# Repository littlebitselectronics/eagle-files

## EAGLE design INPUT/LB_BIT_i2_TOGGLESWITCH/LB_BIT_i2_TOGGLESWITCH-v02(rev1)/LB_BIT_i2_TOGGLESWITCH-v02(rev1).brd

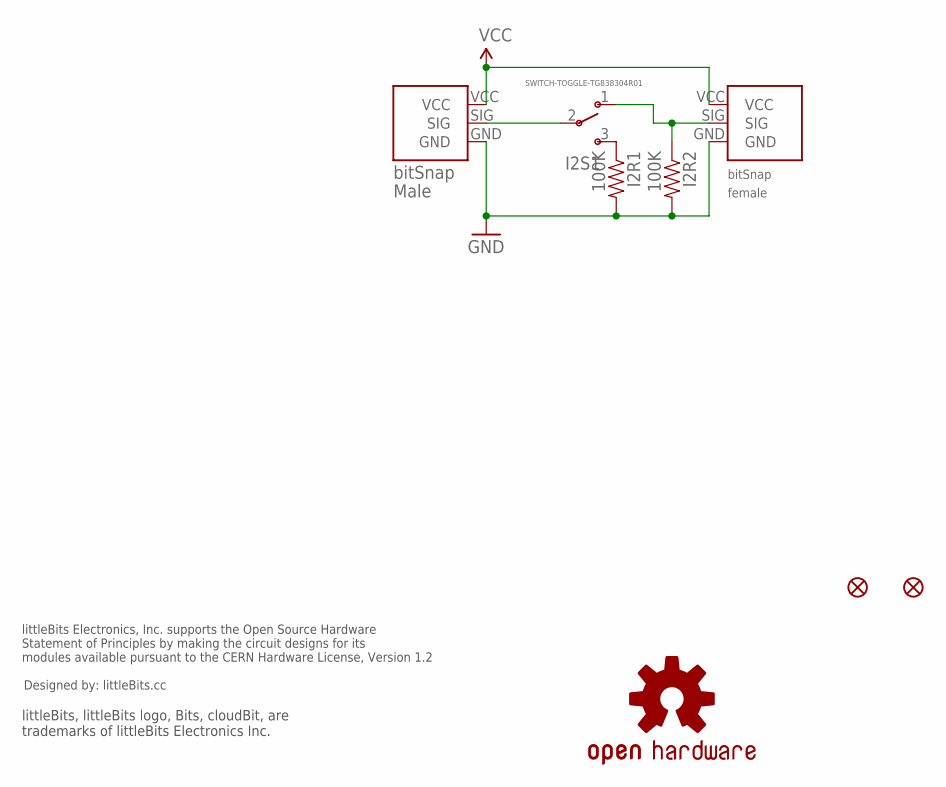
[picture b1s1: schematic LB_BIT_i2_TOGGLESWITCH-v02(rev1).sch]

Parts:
I2BSF: BITSNAP_FEMALE
I2BSM: BITSNAP_MALE
I2R1, I2R2: 100K; 0603-RES
I2S1: SWITCH-TOGGLE-TG838304R01
JP1, JP2: FIDUCIAL1X2; FIDUCIAL-1X2
U$4: OSHWCREDIT
U$7: OSHW-LOGOL; OSHW-LOGO-L

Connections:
GND: I2BSF.GND, I2BSM.GND, I2R1.2, I2R2.2
unnamed: I2R1.1, I2S1.3 (S)
unnamed: I2BSM.SIG, I2S1.2
unnamed: I2BSF.SIG, I2R2.1, I2S1.1 (O)
VCC: I2BSF.VCC, I2BSM.VCC

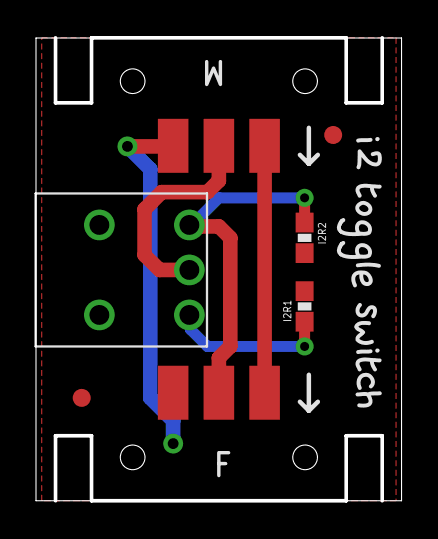
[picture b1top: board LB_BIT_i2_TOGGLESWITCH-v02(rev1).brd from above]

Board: 2 copper layers, 20.3 x 25.7 mm, 24 parts (0 on the bottom side), 5 nets.

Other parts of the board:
U$1, U$29: I
U$2: 2
U$3, U$30: T
U$6: OSHW_FILLX150_NOTEXT
U$22: O
U$23, U$24: G
U$25: L
U$26: E
U$27: S
U$28: W
U$31: C
U$32: H

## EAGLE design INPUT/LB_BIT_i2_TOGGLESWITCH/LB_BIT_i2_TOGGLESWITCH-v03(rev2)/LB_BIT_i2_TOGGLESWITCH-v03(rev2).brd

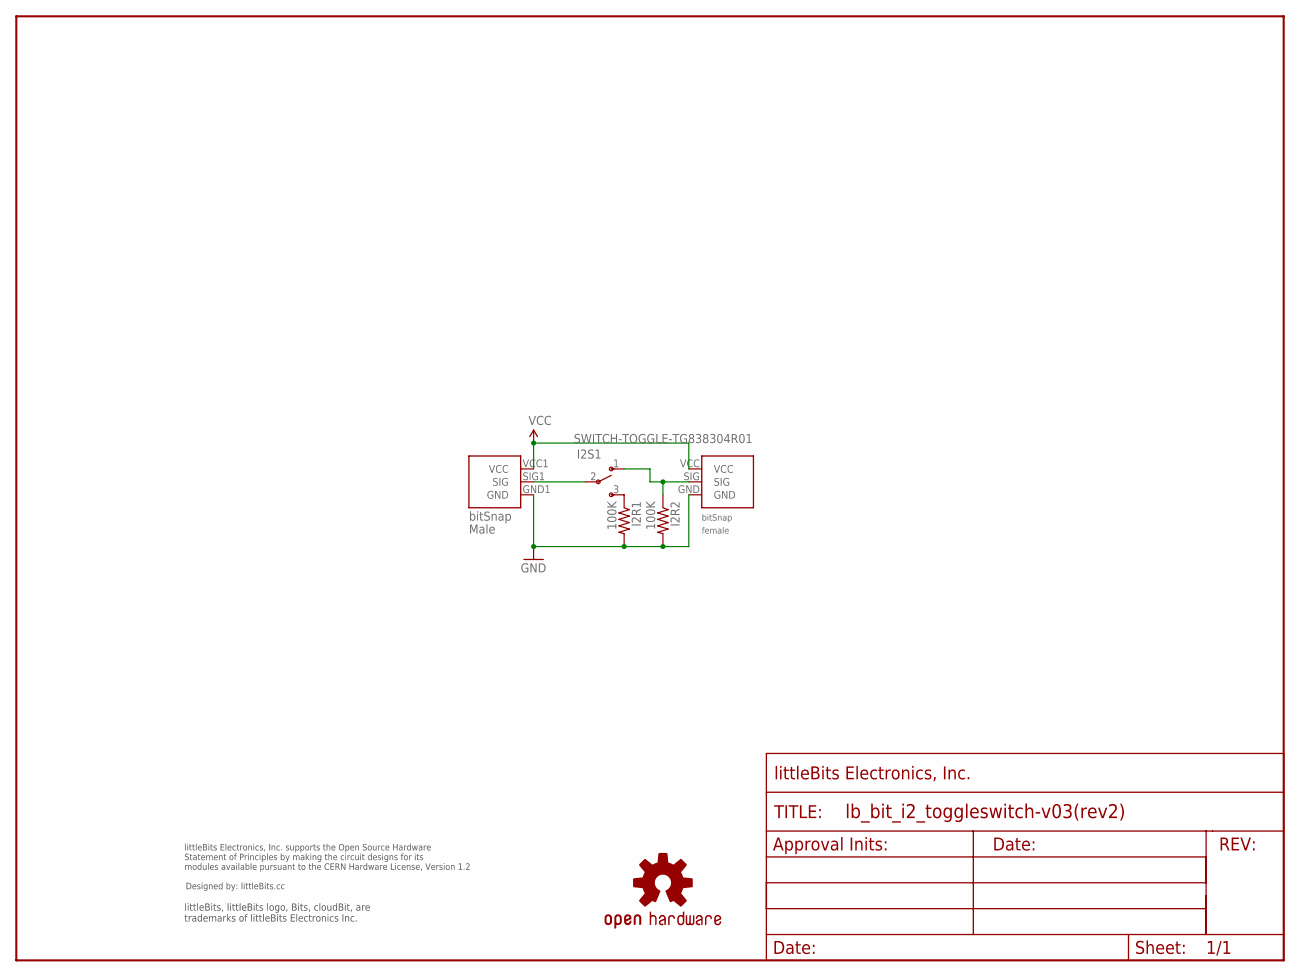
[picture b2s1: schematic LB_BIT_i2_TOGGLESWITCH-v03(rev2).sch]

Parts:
FRAME1: FRAME-LETTER-OHWOHW; FABDWG01-OHW
I2BSF1: BITSNAP_V03_FEMALE
I2BSM1: BITSNAP_V03_MALE
I2R1, I2R2: 100K; 0603-RES
I2S1: SWITCH-TOGGLE-TG838304R01
U$2: OSHWCREDIT
U$7: OSHW-LOGOL; OSHW-LOGO-L

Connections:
GND: I2BSF1.GND, I2BSM1.GND1 (GND), I2R1.2, I2R2.2
unnamed: I2R1.1, I2S1.3 (S)
unnamed: I2BSM1.SIG1 (SIG), I2S1.2
unnamed: I2BSF1.SIG, I2R2.1, I2S1.1 (O)
VCC: I2BSF1.VCC, I2BSM1.VCC1 (VCC)

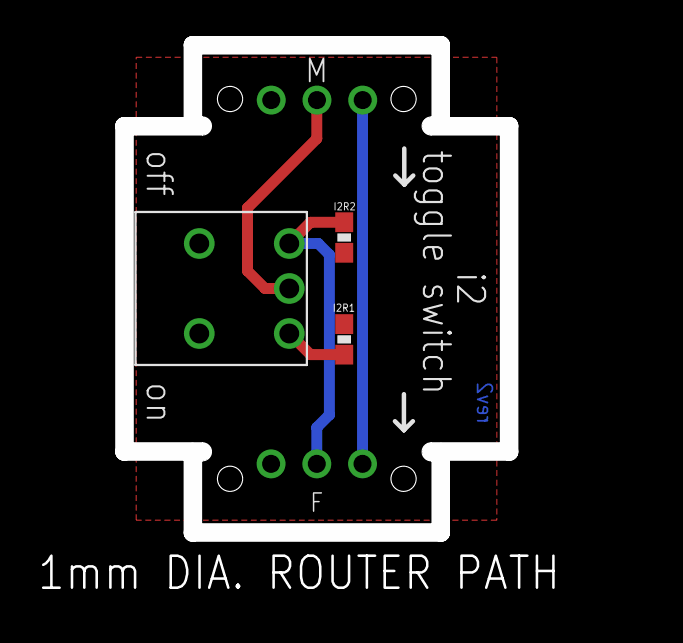
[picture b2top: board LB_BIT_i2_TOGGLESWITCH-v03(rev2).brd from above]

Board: 2 copper layers, 21.4 x 27.1 mm, 9 parts (0 on the bottom side), 5 nets.

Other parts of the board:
U$6: OSHW_FILLX150_NOTEXT

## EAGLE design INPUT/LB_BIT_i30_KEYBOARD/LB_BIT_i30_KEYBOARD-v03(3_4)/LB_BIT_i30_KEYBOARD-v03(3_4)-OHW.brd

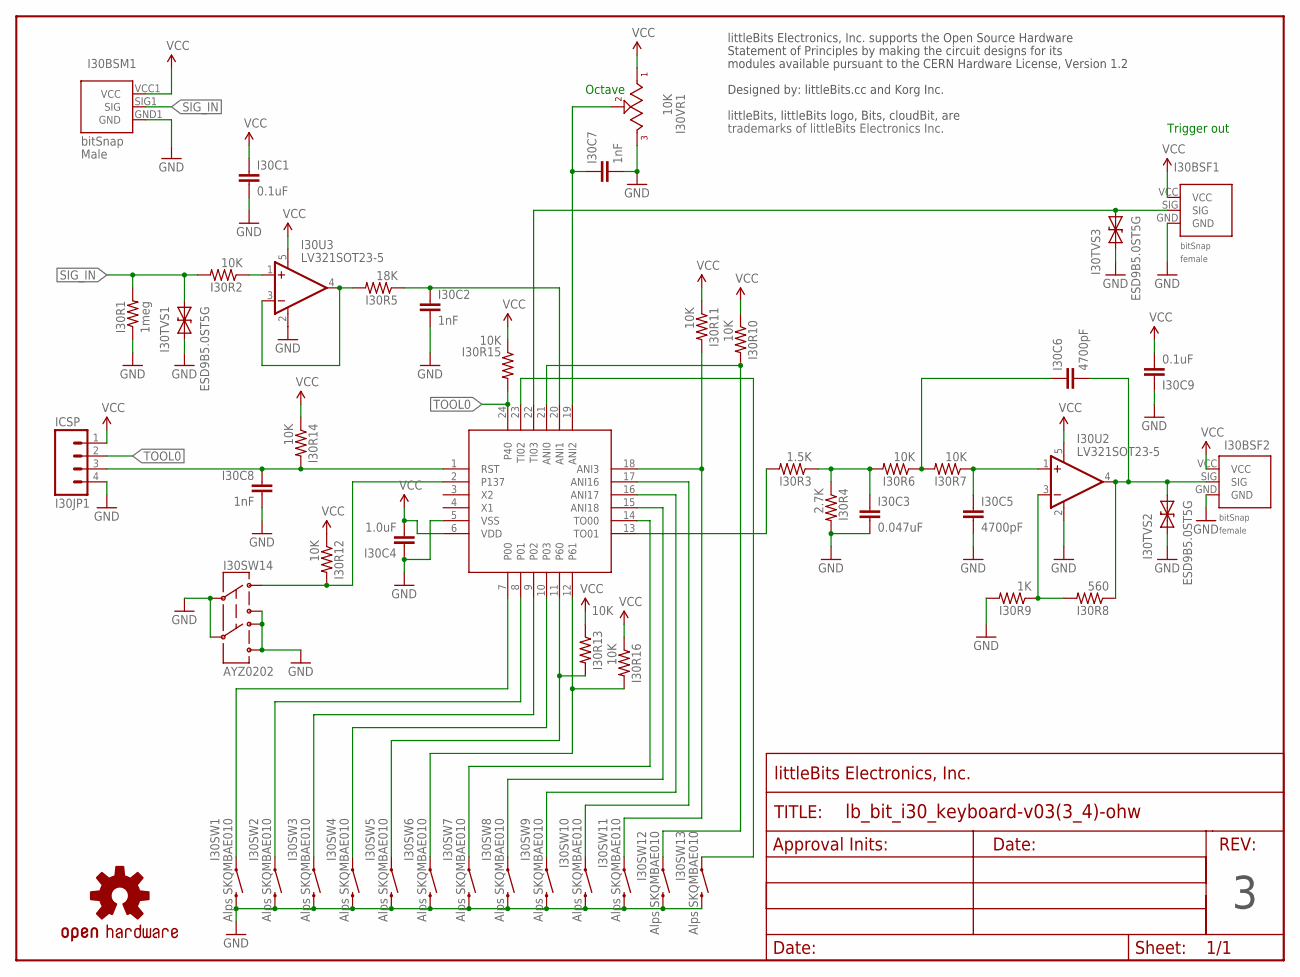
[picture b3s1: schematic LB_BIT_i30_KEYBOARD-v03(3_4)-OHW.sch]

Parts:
FRAME1: FRAME-LETTER-OHWOHW; FABDWG01-OHW
I30BSF1, I30BSF2: BITSNAP_V03_FEMALE
I30BSM1: BITSNAP_V03_MALE
I30C1, I30C9: 0.1uF; CAP-0603
I30C2, I30C7, I30C8: 1nF; CAP-0603
I30C3: 0.047uF; CAP-0603
I30C4: 1.0uF; CAP-0603
I30C5, I30C6: 4700pF; CAP-0603
I30JP1: ICSP; SIP4-SM-0.1IN-NOS.S.
I30R1: 1meg; RES-0603
I30R2, I30R6, I30R7, I30R10, I30R11, I30R12, I30R13, I30R14, I30R15, I30R16: 10K; RES-0603
I30R3: 1.5K; RES-0603
I30R4: 2.7K; RES-0603
I30R5: 18K; RES-0603
I30R8: 560; RES-0603
I30R9: 1K; RES-0603
I30SW1, I30SW2, I30SW3, I30SW4, I30SW5, I30SW6, I30SW7, I30SW8, I30SW9, I30SW10, I30SW11, I30SW12, I30SW13: Alps SKQMBAE010; TACTILE-SWITCH-EVQ-PE104K
I30SW14: AYZ0202
I30TVS1, I30TVS2, I30TVS3: ESD9B5.0ST5G; SOD-923
I30U1: R5F10278QFN-24; QFN-24(4MM)
I30U2, I30U3: LV321SOT23-5; SOT23-5
I30VR1: 10K; THUMBPOT-BOURNS_3352
U$1: OSHW-LOGOL; OSHW-LOGO-L
U$2: OSHWCREDIT-KORG

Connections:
GND: I30BSF1.GND, I30BSF2.GND, I30BSM1.GND1 (GND), I30C1.2, I30C2.2, I30C3.2, I30C4.1, I30C5.2, I30C7.2, I30C8.2, I30C9.1, I30JP1.4, I30R1.1, I30R4.2, I30R9.2, I30SW1.P$2 (2), I30SW2.P$2 (2), I30SW3.P$2 (2), I30SW4.P$2 (2), I30SW5.P$2 (2), I30SW6.P$2 (2), I30SW7.P$2 (2), I30SW8.P$2 (2), I30SW9.P$2 (2), I30SW10.P$2 (2), I30SW11.P$2 (2), I30SW12.P$2 (2), I30SW13.P$2 (2), I30SW14.2, I30SW14.3, I30SW14.4, I30SW14.5, I30SW14.6, I30TVS1.1 (A), I30TVS2.1 (A), I30TVS3.1 (A), I30U1.5 (VSS), I30U2.2 (V-), I30U3.2 (V-), I30VR1.1 (3)
unnamed: I30C2.1, I30R5.1, I30U1.20 (ANI1)
unnamed: I30R5.2, I30U3.3 (-IN), I30U3.4 (OUT)
unnamed: I30C3.1, I30R3.1, I30R4.1, I30R6.2
unnamed: I30R2.1, I30U3.1 (+IN)
unnamed: I30R3.2, I30U1.13 (TO01)
unnamed: I30R8.2, I30R9.1, I30U2.3 (-IN)
unnamed: I30C6.1, I30R6.1, I30R7.2
unnamed: I30BSF1.SIG, I30TVS3.2 (C), I30U1.22 (TI03)
unnamed: I30SW13.P$1 (1), I30U1.23 (TI02)
unnamed: I30C5.1, I30R7.1, I30U2.1 (+IN)
unnamed: I30R12.2, I30SW14.1, I30U1.2 (P137)
unnamed: I30R10.2, I30SW12.P$1 (1), I30U1.21 (ANI0)
unnamed: I30R11.2, I30SW11.P$1 (1), I30U1.18 (ANI3)
unnamed: I30SW10.P$1 (1), I30U1.17 (ANI16)
unnamed: I30SW9.P$1 (1), I30U1.16 (ANI17)
unnamed: I30SW8.P$1 (1), I30U1.15 (ANI18)
unnamed: I30SW7.P$1 (1), I30U1.14 (TO00)
unnamed: I30R16.2, I30SW6.P$1 (1), I30U1.12 (P61)
unnamed: I30R13.2, I30SW5.P$1 (1), I30U1.11 (P60)
unnamed: I30SW4.P$1 (1), I30U1.10 (P03)
unnamed: I30SW3.P$1 (1), I30U1.9 (P02)
unnamed: I30SW2.P$1 (1), I30U1.8 (P01)
unnamed: I30SW1.P$1 (1), I30U1.7 (P00)
unnamed: I30C7.1, I30U1.19 (ANI2), I30VR1.2
unnamed: I30C8.1, I30JP1.3, I30R14.2, I30U1.1 (RST)
SIG_IN: I30BSM1.SIG1 (SIG), I30R1.2, I30R2.2, I30TVS1.2 (C)
SIG_OUT: I30BSF2.SIG, I30C6.2, I30R8.1, I30TVS2.2 (C), I30U2.4 (OUT)
TOOL0: I30JP1.2, I30R15.2, I30U1.24 (P40)
VCC: I30BSF1.VCC, I30BSF2.VCC, I30BSM1.VCC1 (VCC), I30C1.1, I30C4.2, I30C9.2, I30JP1.1, I30R10.1, I30R11.1, I30R12.1, I30R13.1, I30R14.1, I30R15.1, I30R16.1, I30U1.6 (VDD), I30U2.5 (V+), I30U3.5 (V+), I30VR1.3 (1)

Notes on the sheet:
Octave
Trigger out

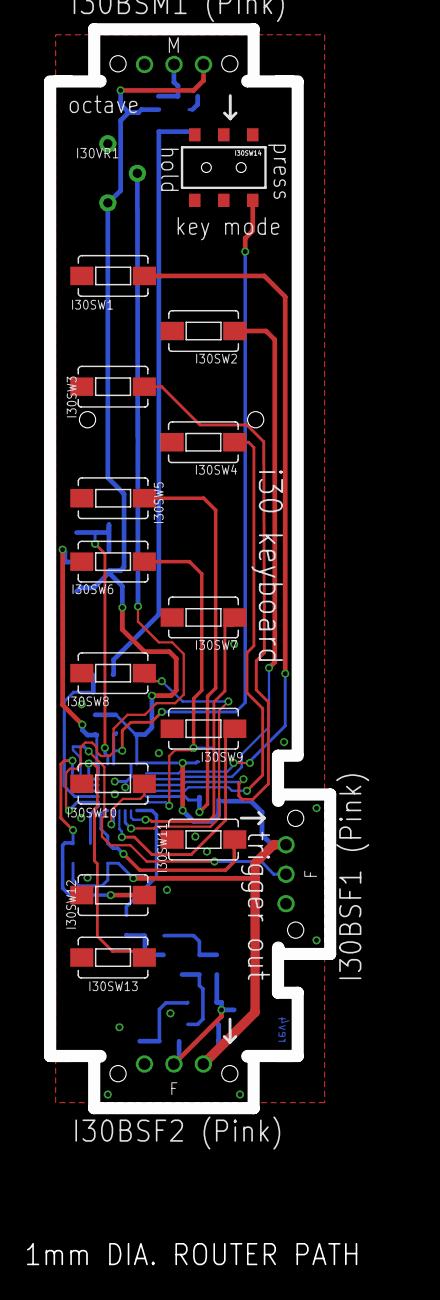
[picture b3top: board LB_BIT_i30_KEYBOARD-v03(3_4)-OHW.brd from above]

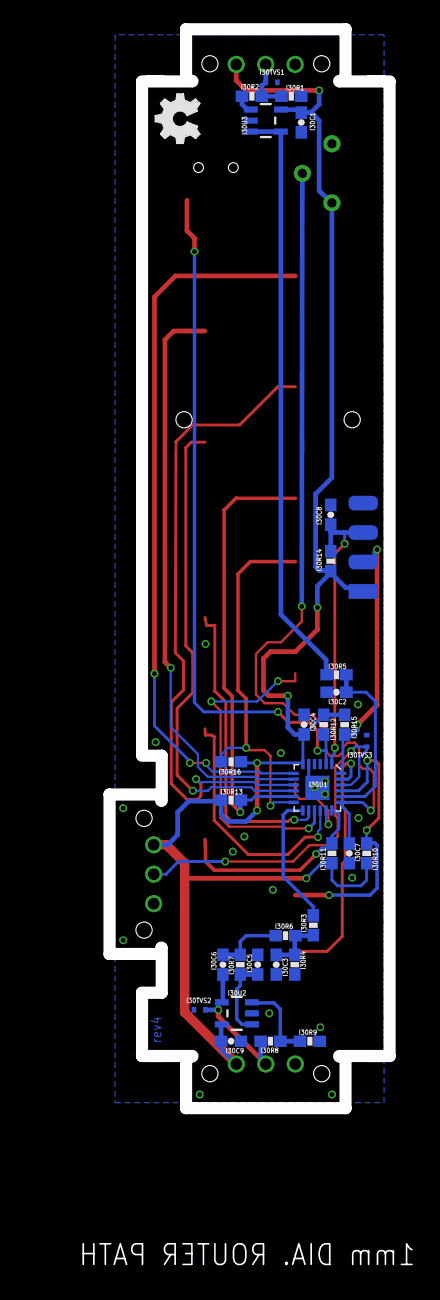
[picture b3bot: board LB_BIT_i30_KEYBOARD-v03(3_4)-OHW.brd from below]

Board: 2 copper layers, 23.2 x 92.1 mm, 55 parts (32 on the bottom side), 30 nets.

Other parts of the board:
U$4: LB_PWR_LEGS
U$17: OSHW_FILLX150_NOTEXT

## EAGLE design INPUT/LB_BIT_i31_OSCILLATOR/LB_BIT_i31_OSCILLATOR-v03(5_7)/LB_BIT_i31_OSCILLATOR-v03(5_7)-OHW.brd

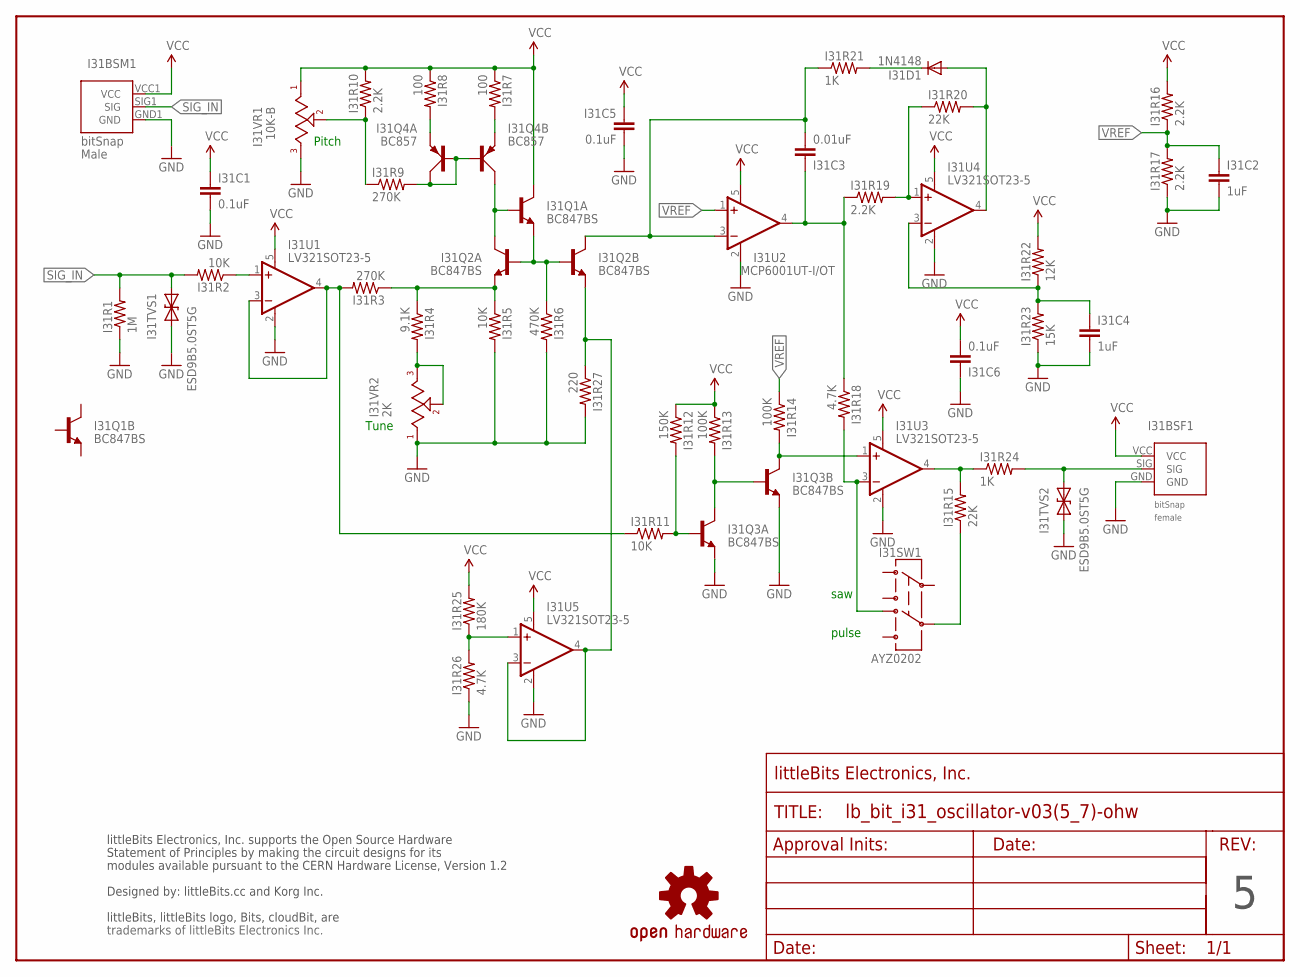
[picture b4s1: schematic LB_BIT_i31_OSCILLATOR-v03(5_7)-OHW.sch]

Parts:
I31BSF1: BITSNAP_V03_FEMALE
I31BSM1: BITSNAP_V03_MALE
I31C1, I31C5, I31C6: 0.1uF; CAP-0603
I31C2, I31C4: 1uF; CAP-0603
I31C3: 0.01uF; CAP-0603
I31D1: 1N4148; SOD-323
I31Q1, I31Q2, I31Q3: BC847BS; SOT-363_PHILLIPS
I31Q4: BC857; SOT-363_PHILLIPS
I31R1: 1M; RES-0603
I31R2, I31R5, I31R11: 10K; RES-0603
I31R3, I31R9: 270K; RES-0603
I31R4: 9.1K; RES-0603
I31R6: 470K; RES-0603
I31R7, I31R8: 100; RES-0603
I31R10, I31R16, I31R17, I31R19: 2.2K; RES-0603
I31R12: 150K; RES-0603
I31R13, I31R14: 100K; RES-0603
I31R15, I31R20: 22K; RES-0603
I31R18, I31R26: 4.7K; RES-0603
I31R21, I31R24: 1K; RES-0603
I31R22: 12K; RES-0603
I31R23: 15K; RES-0603
I31R25: 180K; RES-0603
I31R27: 220; RES-0603
I31SW1: AYZ0202
I31TVS1, I31TVS2: ESD9B5.0ST5G; SOD-923
I31U1, I31U3, I31U4, I31U5: LV321SOT23-5; SOT23-5
I31U2: MCP6001UT; SOT23-5
I31VR1: 10K-B; ALPS_POT
I31VR2: 2K; THUMBPOT-BOURNS_3352
U$2: FRAME-LETTER-OHWOHW; FABDWG01-OHW
U$3: OSHW-LOGOL; OSHW-LOGO-L
U$4: OSHWCREDIT-KORG

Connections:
GND: I31BSF1.GND, I31BSM1.GND1 (GND), I31C1.2, I31C2.2, I31C4.2, I31C5.2, I31C6.1, I31Q3.1 (E), I31Q3.4 (E), I31R1.1, I31R5.2, I31R6.2, I31R17.1, I31R23.1, I31R26.1, I31R27.2, I31TVS1.1 (A), I31TVS2.1 (A), I31U1.2 (V-), I31U2.2 (V-), I31U3.2 (V-), I31U4.2 (V-), I31U5.2 (V-), I31VR1.3, I31VR2.3 (1)
unnamed: I31R4.2, I31VR2.1 (3), I31VR2.2
unnamed: I31R3.2, I31R11.1, I31U1.3 (-IN), I31U1.4 (OUT)
unnamed: I31Q1.2 (B), I31Q2.6 (C), I31Q4.3 (C)
unnamed: I31R2.1, I31U1.1 (+IN)
unnamed: I31Q1.1 (E), I31Q2.2 (B), I31Q2.5 (B), I31R6.1
unnamed: I31Q4.1 (E), I31R8.2
unnamed: I31Q4.4 (E), I31R7.2
unnamed: I31Q2.1 (E), I31R3.1, I31R4.1, I31R5.1
unnamed: I31R18.2, I31SW1.4, I31U3.3 (-IN)
unnamed: I31Q3.2 (B), I31R11.2, I31R12.2
unnamed: I31R19.2, I31R20.1, I31U4.1 (+IN)
unnamed: I31Q4.2 (B), I31Q4.5 (B), I31Q4.6 (C), I31R9.2
unnamed: I31R9.1, I31R10.1, I31VR1.2
unnamed: I31Q3.5 (B), I31Q3.6 (C), I31R13.2
unnamed: I31C3.1, I31R18.1, I31R19.1, I31U2.4 (OUT)
unnamed: I31Q3.3 (C), I31R14.2, I31U3.1 (+IN)
unnamed: I31R15.1, I31SW1.5
unnamed: I31C3.2, I31Q2.3 (C), I31R21.1, I31U2.3 (-IN)
unnamed: I31D1.2 (A), I31R20.2, I31U4.4 (OUT)
unnamed: I31D1.1 (C), I31R21.2
unnamed: I31R15.2, I31R24.1, I31U3.4 (OUT)
unnamed: I31C4.1, I31R22.1, I31R23.2, I31U4.3 (-IN)
unnamed: I31Q2.4 (E), I31R27.1, I31U5.3 (-IN), I31U5.4 (OUT)
unnamed: I31R25.1, I31R26.2, I31U5.1 (+IN)
SIG_IN: I31BSM1.SIG1 (SIG), I31R1.2, I31R2.2, I31TVS1.2 (C)
SIG_OUT: I31BSF1.SIG, I31R24.2, I31TVS2.2 (C)
VCC: I31BSF1.VCC, I31BSM1.VCC1 (VCC), I31C1.1, I31C5.1, I31C6.2, I31Q1.6 (C), I31R7.1, I31R8.1, I31R10.2, I31R12.1, I31R13.1, I31R16.2, I31R22.2, I31R25.2, I31U1.5 (V+), I31U2.5 (V+), I31U3.5 (V+), I31U4.5 (V+), I31U5.5 (V+), I31VR1.1
VREF: I31C2.1, I31R14.1, I31R16.1, I31R17.2, I31U2.1 (+IN)

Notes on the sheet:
pulse
saw
Pitch
Tune
MCP6001UT-I/OT

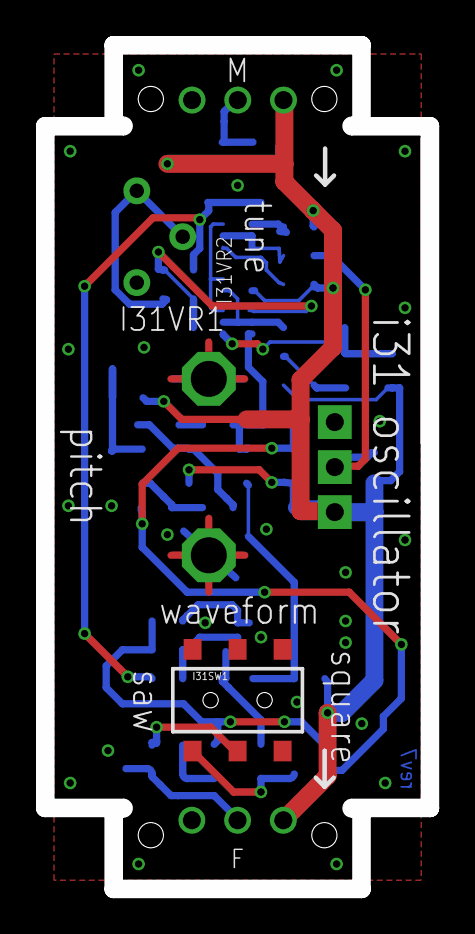
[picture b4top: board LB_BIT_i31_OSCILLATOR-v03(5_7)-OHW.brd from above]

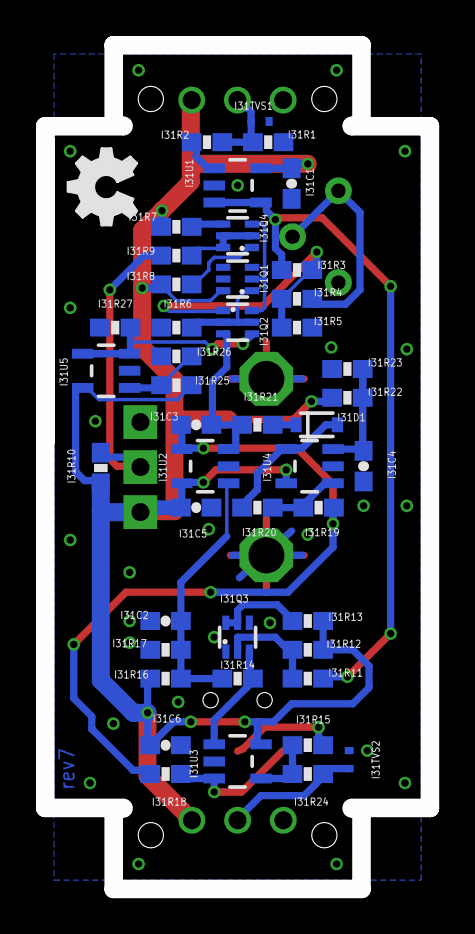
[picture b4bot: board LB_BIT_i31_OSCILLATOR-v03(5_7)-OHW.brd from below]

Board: 2 copper layers, 21.4 x 46.9 mm, 54 parts (45 on the bottom side), 29 nets.

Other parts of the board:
U$8: OSHW_FILLX150_NOTEXT

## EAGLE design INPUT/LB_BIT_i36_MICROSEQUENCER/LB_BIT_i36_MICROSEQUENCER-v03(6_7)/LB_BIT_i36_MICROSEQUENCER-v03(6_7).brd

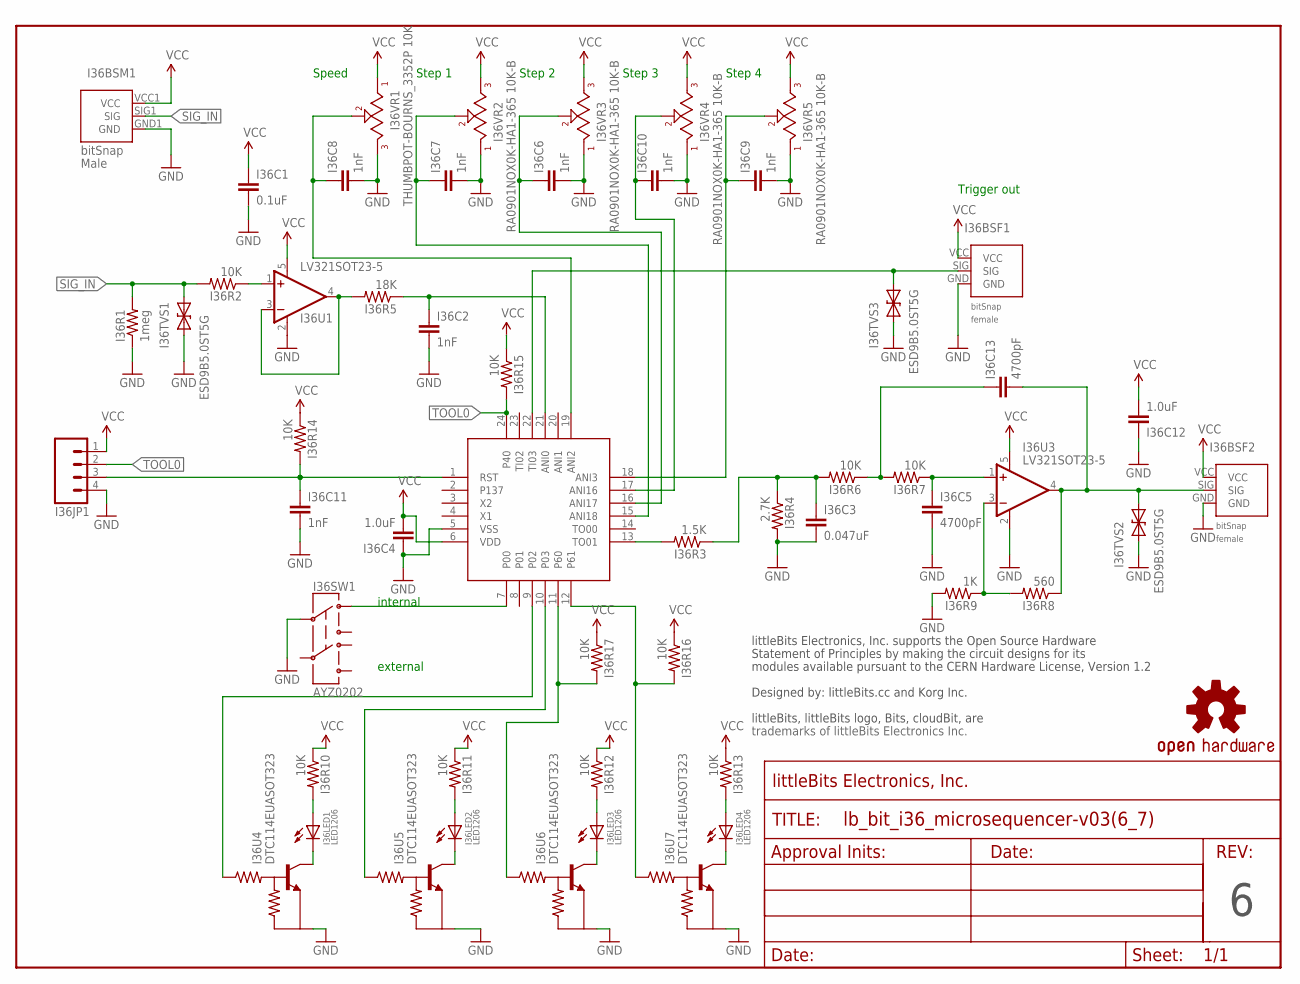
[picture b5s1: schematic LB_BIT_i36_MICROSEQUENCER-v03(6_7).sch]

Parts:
I36BSF1, I36BSF2: BITSNAP_V03_FEMALE
I36BSM1: BITSNAP_V03_MALE
I36C1: 0.1uF; CAP-0603
I36C2, I36C6, I36C7, I36C8, I36C9, I36C10, I36C11: 1nF; CAP-0603
I36C3: 0.047uF; CAP-0603
I36C4, I36C12: 1.0uF; CAP-0603
I36C5, I36C13: 4700pF; CAP-0603
I36JP1: HDR-4SM_SML; SIP4-SM-0.1IN-NOS.S.
I36LED1, I36LED2, I36LED3, I36LED4: LED1206; LED-1206
I36R1: 1meg; RES-0603
I36R2, I36R6, I36R7, I36R10, I36R11, I36R12, I36R13, I36R14, I36R15, I36R16, I36R17: 10K; RES-0603
I36R3: 1.5K; RES-0603
I36R4: 2.7K; RES-0603
I36R5: 18K; RES-0603
I36R8: 560; RES-0603
I36R9: 1K; RES-0603
I36SW1: AYZ0202
I36TVS1, I36TVS2, I36TVS3: ESD9B5.0ST5G; SOD-923
I36U1, I36U3: LV321SOT23-5; SOT23-5
I36U2: R5F10278QFN-24; QFN-24(4MM)
I36U4, I36U5, I36U6, I36U7: DTC114EUASOT323; SOT323
I36VR1: THUMBPOT-BOURNS_3352P 10K; THUMBPOT-BOURNS_3352
I36VR2, I36VR3, I36VR4, I36VR5: RA0901NOX0K-HA1-365 10K-B; ALPS_POT
U$1: OSHWCREDIT-KORG
U$2: OSHW-LOGOL; OSHW-LOGO-L
U$3: FRAME-LETTER-OHWOHW; FABDWG01-OHW

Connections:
GND: I36BSF1.GND, I36BSF2.GND, I36BSM1.GND1 (GND), I36C1.2, I36C2.2, I36C3.2, I36C4.1, I36C5.2, I36C6.2, I36C7.2, I36C8.2, I36C9.2, I36C10.2, I36C11.2, I36C12.1, I36JP1.4, I36R1.1, I36R4.2, I36R9.2, I36SW1.2, I36TVS1.1 (A), I36TVS2.1 (A), I36TVS3.1 (A), I36U1.2 (V-), I36U2.5 (VSS), I36U3.2 (V-), I36U4.GND (E), I36U5.GND (E), I36U6.GND (E), I36U7.GND (E), I36VR1.1 (3), I36VR2.1, I36VR3.1, I36VR4.1, I36VR5.1
unnamed: I36C2.1, I36R5.1, I36U2.21 (ANI0)
unnamed: I36R5.2, I36U1.3 (-IN), I36U1.4 (OUT)
unnamed: I36C3.1, I36R3.1, I36R4.1, I36R6.2
unnamed: I36R2.1, I36U1.1 (+IN)
unnamed: I36R3.2, I36U2.13 (TO01)
unnamed: I36R8.2, I36R9.1, I36U3.3 (-IN)
unnamed: I36C13.1, I36R6.1, I36R7.2
unnamed: I36BSF1.SIG, I36TVS3.2 (C), I36U2.22 (TI03)
unnamed: I36C5.1, I36R7.1, I36U3.1 (+IN)
unnamed: I36SW1.1, I36U2.7 (P00)
unnamed: I36C7.1, I36U2.15 (ANI18), I36VR2.2
unnamed: I36C6.1, I36U2.16 (ANI17), I36VR3.2
unnamed: I36U2.9 (P02), I36U4.IN (1)
unnamed: I36U2.10 (P03), I36U5.IN (1)
unnamed: I36R17.2, I36U2.11 (P60), I36U6.IN (1)
unnamed: I36R16.2, I36U2.12 (P61), I36U7.IN (1)
unnamed: I36LED1.A, I36R10.2
unnamed: I36LED1.C, I36U4.OUT (C)
unnamed: I36LED2.A, I36R11.2
unnamed: I36LED2.C, I36U5.OUT (C)
unnamed: I36LED3.A, I36R12.2
unnamed: I36LED3.C, I36U6.OUT (C)
unnamed: I36LED4.A, I36R13.2
unnamed: I36LED4.C, I36U7.OUT (C)
unnamed: I36C8.1, I36U2.19 (ANI2), I36VR1.2
unnamed: I36C10.1, I36U2.17 (ANI16), I36VR4.2
unnamed: I36C9.1, I36U2.18 (ANI3), I36VR5.2
unnamed: I36C11.1, I36JP1.3, I36R14.2, I36U2.1 (RST)
SIG_IN: I36BSM1.SIG1 (SIG), I36R1.2, I36R2.2, I36TVS1.2 (C)
SIG_OUT: I36BSF2.SIG, I36C13.2, I36R8.1, I36TVS2.2 (C), I36U3.4 (OUT)
TOOL0: I36JP1.2, I36R15.2, I36U2.24 (P40)
VCC: I36BSF1.VCC, I36BSF2.VCC, I36BSM1.VCC1 (VCC), I36C1.1, I36C4.2, I36C12.2, I36JP1.1, I36R10.1, I36R11.1, I36R12.1, I36R13.1, I36R14.1, I36R15.1, I36R16.1, I36R17.1, I36U1.5 (V+), I36U2.6 (VDD), I36U3.5 (V+), I36VR1.3 (1), I36VR2.3, I36VR3.3, I36VR4.3, I36VR5.3

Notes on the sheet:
Speed
Step 1
Step 2
Step 3
Step 4
internal
external
Trigger out

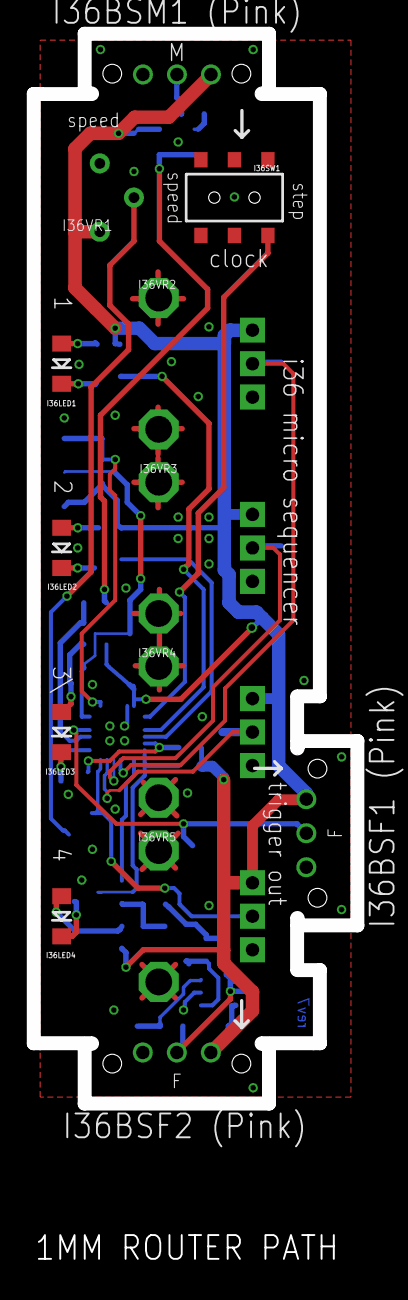
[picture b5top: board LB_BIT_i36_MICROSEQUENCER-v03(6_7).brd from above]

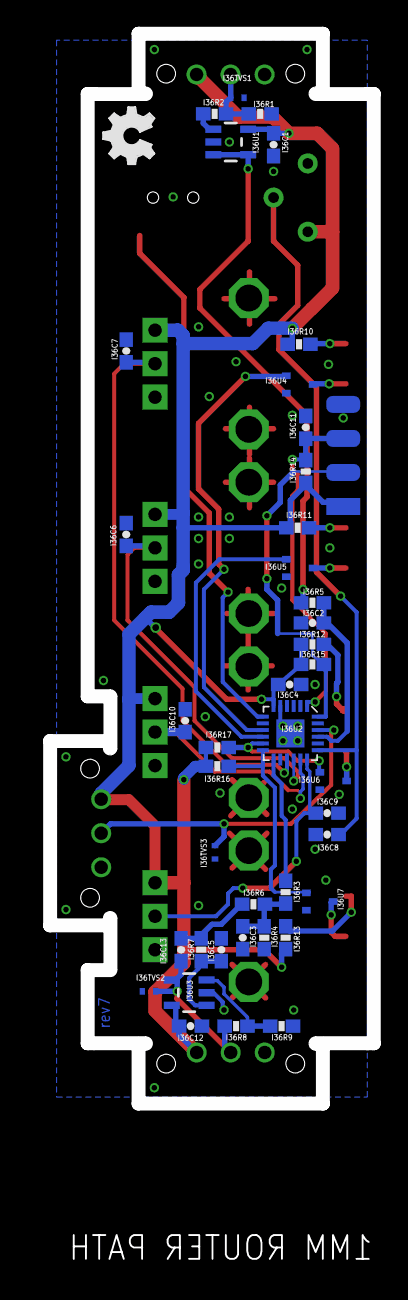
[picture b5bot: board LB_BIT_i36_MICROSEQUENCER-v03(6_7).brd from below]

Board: 2 copper layers, 24.2 x 79.9 mm, 58 parts (41 on the bottom side), 33 nets.

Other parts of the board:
U$17: OSHW_FILLX150_NOTEXT

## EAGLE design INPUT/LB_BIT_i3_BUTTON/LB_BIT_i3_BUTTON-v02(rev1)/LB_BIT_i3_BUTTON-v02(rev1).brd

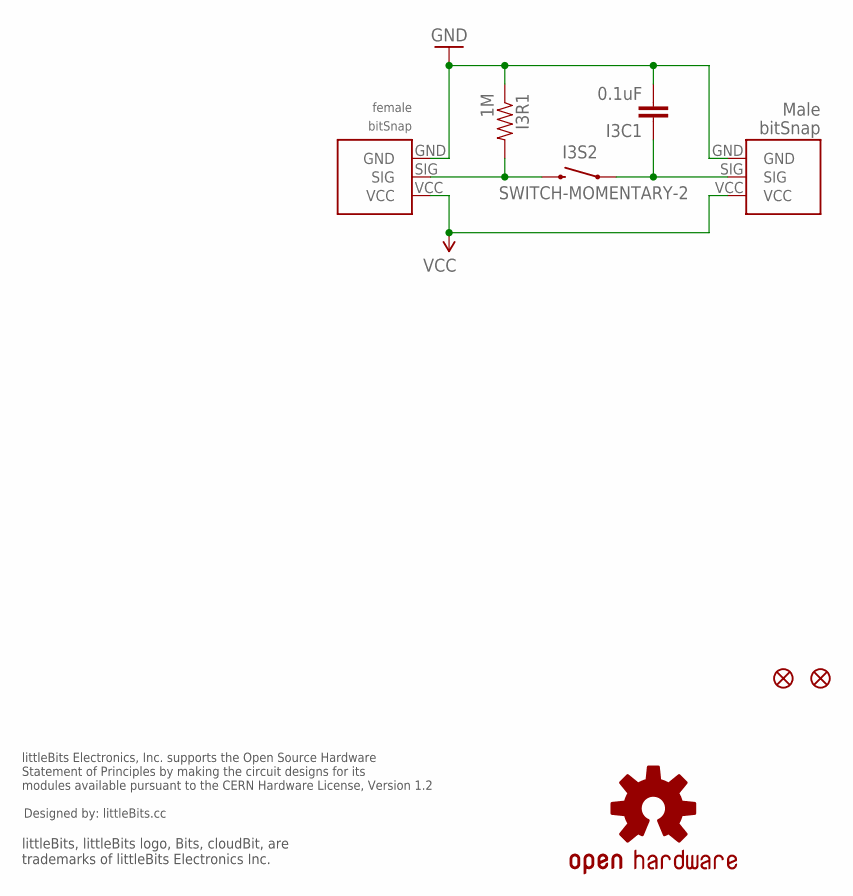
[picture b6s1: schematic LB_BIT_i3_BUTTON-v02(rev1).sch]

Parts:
I3BSF: BITSNAP_FEMALE
I3BSM: BITSNAP_MALE
I3C1: 0.1uF; 0603-CAP
I3R1: 1M; 0603-RES
I3S2: SWITCH-MOMENTARY-2; TACTILE_SWITCH_TALL
JP1, JP2: FIDUCIAL1X2.5; FIDUCIAL-1X2.5
U$1: OSHW-LOGOL; OSHW-LOGO-L
U$2: OSHWCREDIT

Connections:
GND: I3BSF.GND, I3BSM.GND, I3C1.2, I3R1.1
SIG: I3BSF.SIG, I3R1.2, I3S2.B2 (2)
SIG2: I3BSM.SIG, I3C1.1, I3S2.A2 (1)
VCC: I3BSF.VCC, I3BSM.VCC

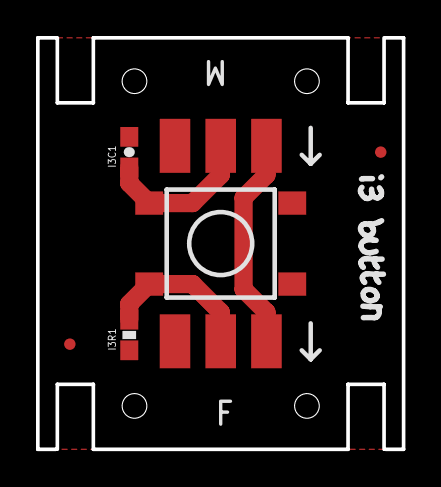
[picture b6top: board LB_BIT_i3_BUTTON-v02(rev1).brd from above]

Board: 2 copper layers, 20.3 x 22.9 mm, 10 parts (0 on the bottom side), 4 nets.

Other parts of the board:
U$3: OSHW_FILLX150_NOTEXT

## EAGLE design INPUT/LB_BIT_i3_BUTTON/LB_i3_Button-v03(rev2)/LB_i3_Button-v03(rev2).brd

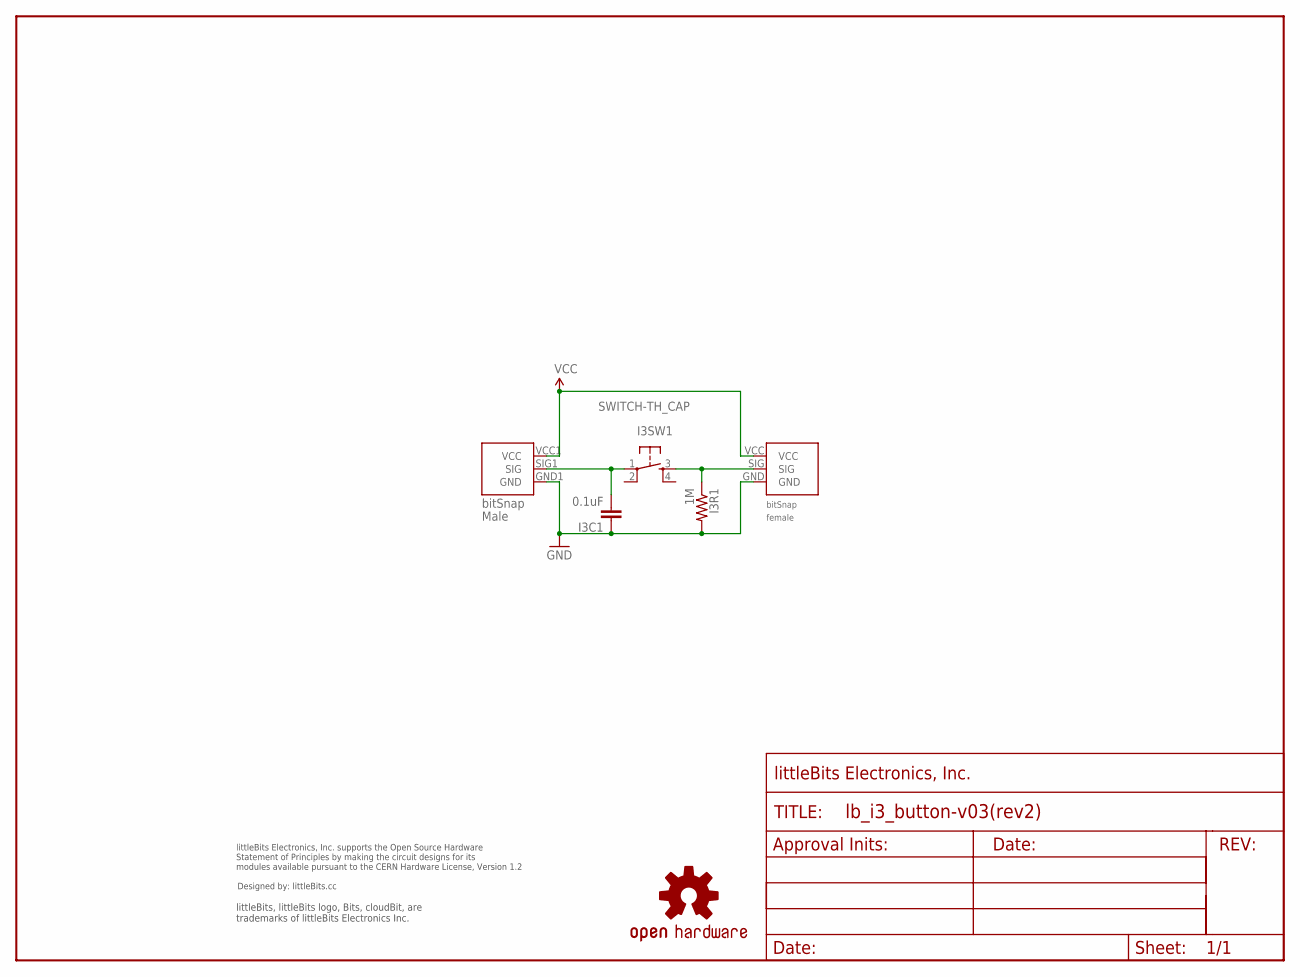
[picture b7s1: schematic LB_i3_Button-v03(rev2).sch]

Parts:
I3BSF1: BITSNAP_V03_FEMALE
I3BSM1: BITSNAP_V03_MALE
I3C1: 0.1uF; 0603-CAP
I3R1: 1M; 0603-RES
I3SW1: SWITCH-TH_CAP
U$1: OSHW-LOGOL; OSHW-LOGO-L
U$2: FRAME-LETTER-OHWOHW; FABDWG01-OHW
U$5: LB_CREDITS; OSHWCREDIT

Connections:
GND: I3BSF1.GND, I3BSM1.GND1 (GND), I3C1.1, I3R1.2
SIG: I3BSM1.SIG1 (SIG), I3C1.2, I3SW1.1
SIG2: I3BSF1.SIG, I3R1.1, I3SW1.3
VCC: I3BSF1.VCC, I3BSM1.VCC1 (VCC)

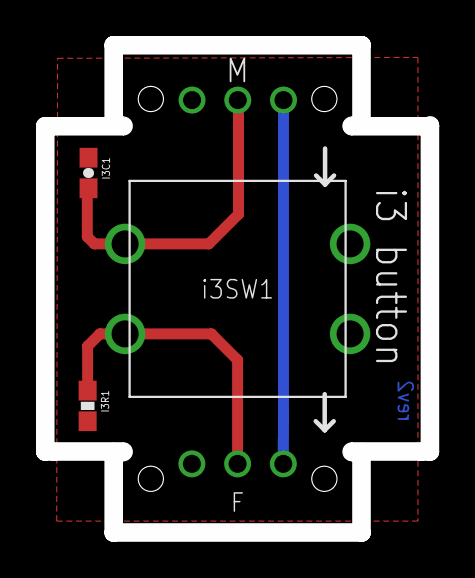
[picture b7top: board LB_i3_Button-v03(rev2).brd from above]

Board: 2 copper layers, 21.4 x 27.1 mm, 9 parts (0 on the bottom side), 4 nets.

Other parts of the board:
U$3: OSHW_FILLX150_NOTEXT

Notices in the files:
parts and their libraries:
LITTLEBITS: modules available pursuant to the CERN Hardware License,
Version 1.2
SparkFun_NEW: Licensing: CC v3.0 Share-Alike You are welcome to use this library for commercial purposes.
LITTLEBITS: modules available pursuant to the CERN Hardware License, Version 1.2
